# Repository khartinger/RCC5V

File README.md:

<table><tr><td></img></td><td>
Last modified: 2025-11-21 <br>   
<h1>Controlling model railroad components with DCC, MQTT and manually</h1>
<a href="LIESMICH.md">==> Deutsche Version</a>&nbsp; &nbsp; &nbsp; 
</td></tr></table>   

[Directly to the table of contents of this repository](#x20)   

# Introduction
Switching points is an important part of model railroading. There are many ways to control turnouts, uncouplers, disconnectable tracks and other components. Who doesn't want to be able to do this in different ways?    
The following image shows a part of an RCC control (RCC = Railway-Component-Control) with information display, switching and LED feedback.   
   
_Figure 1: Example user interface RCC control unit_   

## Traditional switching of turnouts etc.   
The simplest method of switching is, of course, to do it all by hand. In this case, you don't even need point machines. But with more distant or distributed components, this mode of operation quickly becomes cumbersome.   
For this reason, magnetic drives are usually used to switch the components. In the simplest case, the AC voltage is switched directly:   

_Figure 2: Direct switching of model railway components   
(turnout = turnout, uncoupler = uncoupler track, disconnectable track = disconnectable track)_   

However, direct switching of the AC voltage has disadvantages: There is no feedback on the actual switching status and automatic switching of several components is not possible.   
These disadvantages can be eliminated by commercial, digital control systems. Unfortunately, this is usually associated with considerable costs. For this reason, self-construction is an option, which also offers additional possibilities and flexibility.   

## How to do it better?
If you like building things yourself, you've come to the right place. The low-cost RCC (Railway Component Control) model railroad component controller presented here allows you to switch model railroad components in three different ways:   
* directly on the module or on the layout at the touch of a button   
* via DCC   
* via MQTT commands &uuml;over the WLAN   

In the standard version, up to 32 digital outputs and inputs are available. This means that a maximum of 16 two-way switches or 10 three-way switches etc. can be controlled. This number is normally sufficient for modules.   
Expansion of the system is generally possible and only depends on the I²C-IO expanders used.   

Some skills are advantageous for the successful use of the RCC system:   
* Soldering and some manual dexterity   
* Compiling and uploading a file to an ESP32 microcontroller   
* Basic knowledge of the open source [circuit board layout program KiCad](https://www.kicad.org/)   
* Basic knowledge of MQTT, if MQTT is to be used for control   

# How do I get started?
1. you should first get an overview of the [contents of this repository](#x20) and [the RCC system](#x30). This is provided in the chapters below in this manual.   
2. If the RCC system is the right choice, the requirements for your own system have to be defined:   
* Which components are needed?
* How many of each type are needed?
* Which DCC address for which device?   
_Example demo program_:   
1x uncoupler with DCC address 11, 1x two-way turnout (DCC 21), 1x three-way turnout (DCC 31 and 32), 1x traction current (DCC 41) and 1x flashing light (DCC 51).   
3. the next step is to manufacture the required components. How to do this is described in the chapter [“How do I start the RCC project?” (/fab/rcc0_start/README.md)](/fab/rcc0_start/README.md).   
4. the demo program is then adapted to your own system and the ESP32 microcontroller is programmed. This is described in chapter [`/software/rcc_demo1
/CUSTOMIZE_E.md`](/software/rcc_demo1/CUSTOMIZE_E.md).   
5. Finally, all components are wired and the entire system is tested.   

The detailed description of the [construction of module #12: “passing loop and siding”](/examples/module12/LIESMICH.md) can also be a great help.   

[To the top of the page](#up)   

# Overview
This repository deals with the production and use of components for controlling turnouts, uncouplers, disconnectable tracks etc. on an electric model railroad using DCC, MQTT or manually.   
The following topics are covered in various subdirectories:   

__Information about the system__   
* [How do I begin the RCC project?](/fab/rcc0_start/README.md)   
* [Electrical connection of railroad modules according to NEM 908D](/info/con_NEM908/README.md)   
* [Drill holes and covers for the front of the module](/info/frontpanel/README.md)   

__Manufacturing the system components__   
* [Manufacturing of Components for the power supply](/fab/rcc1_supply/README.md)   
* [Manufacturing of the ESP32-Shields](/fab/rcc2_esp32/README.md)   
* [Manufacturing of i2c boards](/fab/rcc3_i2c/README.md)   
* [Manufacturing of the switching blocks](/fab/rcc4_block/README.md)   
* [Manufacturing of additional boards](/fab/rcc5_add_ons/README.md)   
* [KiCad files of RCC components](/fab/kicad/README.md)   

__Software for the ESP32__   
* [MQTT commands for controlling the components](/software/mqtt/README.md)   
* [Overview of the demo software](/software/rcc_demo1/README.md)   
* [Customize the demo software to your own needs](/software/rcc_demo1/CUSTOMIZE_E.md)   
* [Structure of the demo software in detail](/software/rcc_demo1/DETAILS_E.md)   
* [Automatic execution of MQTT command sequences](/software/mqtt/README.md#x30)   

__Examples, use of the system__   
* [Example wiring of a turnout](/examples/exampleTurnout2/README.md)   
* [Construction of the “RCC block tester”](/examples/blocktester/README.md)   
* [Construction of module 12: “passing loop and siding”](/examples/module12/README.md)   
* [Construction of module 13: “reverse loop - west”](/examples/module13/README.md)   
* [Construction of module 14: “Two tracks to one track”](/examples/module14/README.md)   
* [Conversion of module M01: “Track 1 to 2 with goods shed (2010)”](/examples/module01/README.md)   

__Other practical ideas for modules and the like__   
* [module dust cover](/info/dust_cover/README.md)   

[To the top of the page](#up)   

# The RCC-system at a glance   
The RCC system has a modular structure and mechanically consists of a series of modules or blocks. Logically, it consists of six parts:   

1. __FEED-IN__ (power supply): Generation and provision of the supply voltage (here AC voltage) and the DCC signals for the RCC system by external components.   
2. __SUPPLY__ (module supply): The AC voltage, the traction current and the DCC signal for switching the magnetic articles are taken from the 25-pin plug according to NEM908 and a separate 5V DC voltage is generated.   
3. __&micro;C__ (microcontroller): The microcontroller, equipped with additional shields, is used to control the module. An ESP32 is used, which also handles communication with the MQTT broker.  
4. __I2C__: Connection between the microcontroller and the control blocks (RCC blocks). I2C I/O expander boards with PCF8574 are used for this purpose.   
5. __RCC block__: The control element for _a_ model railroad component with local operating and display elements.   
6. the __model railroad components__ such as turnouts, uncouplers and disconnectable tracks.   

_Figure 3: Block diagram for switching railroad components with 5V_   

By using the I2C-I/O-Expander-Boards it is possible to control several components:   
   
_Figure 4: Block diagram switching several railroad components with 5V_   

# Practical setup
Before e.g. the first switching of a turnout with RCC, some components must first be manufactured. How to do this is described in the chapter [“How do I start the RCC project?” (/fab/rcc0_start/README.md)](/fab/rcc0_start/README.md).   
The following figure shows an example of the modules required to control a three-way turnout:   
   
_Figure 5: Demo setup of an RCC-5V system: the individual parts_   

On the far left you can see the 25-pin connector with the 5V power supply (“SUPPLY”), behind it is the ESP32 with a 1.56 inch display (“&micro;C”). Two I2C-PCF8574 boards (“I2C”) are mounted in the front center, behind them the RCC block. On the right you can see a three-way turnout with two Fleischmann 640000 turnout drives. The electrical connection of the modules is made using 6-pin ribbon cables and wires.   

The following image shows an example of a possible front view of a module:   
   
_Figure 6: Example of module front view (= operating side)_   

[To the top of the page](#up)

# Example: Circuit diagram for switching a turnout with the RCC5V system
The following picture shows the electrical circuit diagram for controlling a turnout with DCC, MQTT or manually. The light green rectangles represent circuit boards developed in KiCad 8.0 and manufactured by [PCB Way](https://www.pcbway.com/). To do this, simply install the PCB Way plug-in in KiCad and the data required for production is then transferred with a click of the mouse.   

_Figure 7 Overall circuit diagram of the RCC-5V system_   

The upper third of the picture shows the supply of the DCC signal and the AC voltage (“FEED-IN”). The DCC signal for the traction current and the digital switching of the points is generated here with an old Roco-Multimaus, a 230V/18V/2.9A transformer [(e.g. BV00/026 from Conrad)](https://www.conrad.at/de/p/bv00-026-hochleistungstransformator-230-v-404288.html?refresh=true) is used for the AC voltage supply.   

The middle third of the picture shows the connection of the 25-pin connector to the microcontroller (5V and DCC signal) and to the RCC blocks (5V and AC signal). The ESP32 operates two separate I2C buses, one for the 1.56” OLED display (with 3.3V) and the second I2C bus for the PCF8574 boards (with 5V).   

Finally, the lower third of the picture shows the control of a two-way switch by an RCC block.   
The RCC block receives the switching command "Straight" (set WSA to 0V) or "Branch" (WSB=0V) from the microcontroller, switches the turnout and returns the state of the turnout (WRA=5V, WRB=0V for “Straight” or WRA=0V, WRB=5V for “Branch”). The RCC block also contains two buttons for local switching of the points and two LEDs for local display of the switching status of the points.   
You can also see that each RCC block requires a 5V and an AC voltage to switch the points.   

[To the top of the page](#up)

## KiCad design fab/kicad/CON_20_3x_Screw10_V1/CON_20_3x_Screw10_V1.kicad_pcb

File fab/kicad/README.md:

<table><tr><td></img></td><td>
Last modified: 2024-11-27 <br>   
<h1>KiCad files of RCC components</h1>
<a href="LIESMICH.md">==> Deutsche Version</a>&nbsp; &nbsp; &nbsp; 
</td></tr></table>    

# ... To Do ...

[To the top of the page](#up)

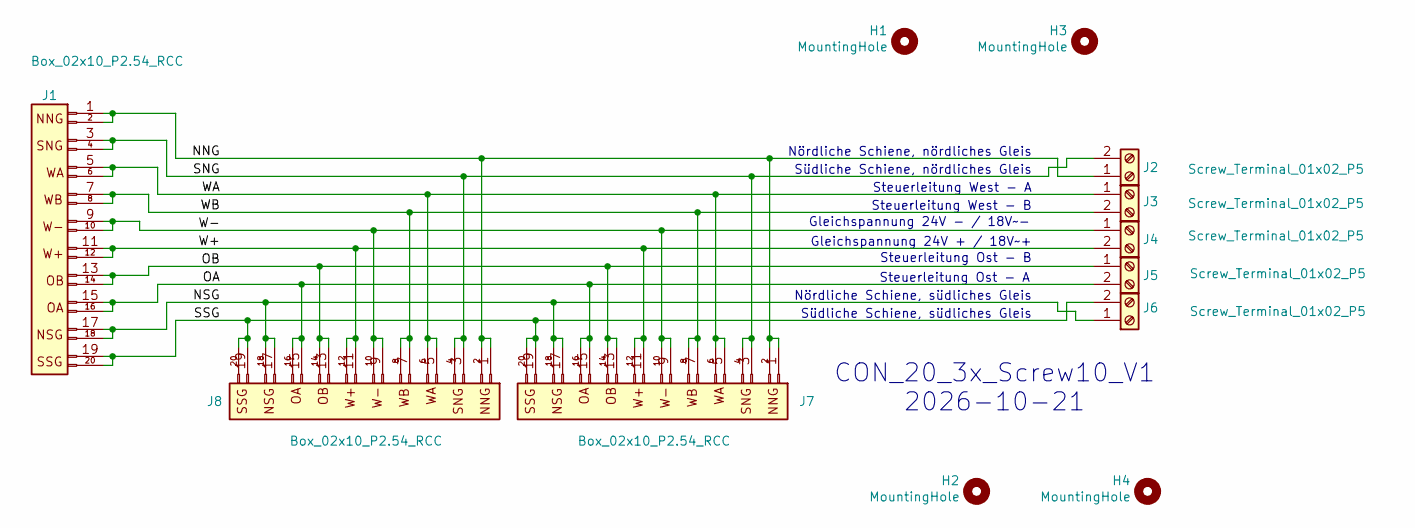
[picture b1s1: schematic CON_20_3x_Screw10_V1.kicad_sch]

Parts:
H1, H2, H3, H4: MountingHole; MountingHole_2.7mm_M2.5_DIN965_Pad_TopBottom
J1, J7, J8: Box_02x10_P2.54_RCC; Box_02x10_P2.54mm_Vertical_kh
J2, J3, J4, J5, J6: Screw_Terminal_01x02_P5

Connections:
/NNG: J1.1, J1.2, J2.1, J7.1, J7.2, J8.1, J8.2
/NSG: J1.17, J1.18, J6.1, J7.17, J7.18, J8.17, J8.18
/OA: J1.15, J1.16, J5.2, J7.15, J7.16, J8.15, J8.16
/OB: J1.13, J1.14, J5.1, J7.13, J7.14, J8.13, J8.14
/SNG: J1.3, J1.4, J2.2, J7.3, J7.4, J8.3, J8.4
/SSG: J1.19, J1.20, J6.2, J7.19, J7.20, J8.19, J8.20
/W+: J1.11, J1.12, J4.2, J7.11, J7.12, J8.11, J8.12
/W-: J1.9, J1.10, J4.1, J7.9, J7.10, J8.9, J8.10
/WA: J1.5, J1.6, J3.1, J7.5, J7.6, J8.5, J8.6
/WB: J1.7, J1.8, J3.2, J7.7, J7.8, J8.7, J8.8

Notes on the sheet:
CON_20_3x_Screw10_V1 2026-10-21
Südliche Schiene, südliches Gleis
Südliche Schiene, nördliches Gleis
Gleichspannung 24V - / 18V~-
Nördliche Schiene, nördliches Gleis
Steuerleitung West - A
Steuerleitung Ost - B
Steuerleitung West - B
Gleichspannung 24V + / 18V~+
Nördliche Schiene, südliches Gleis
Steuerleitung Ost - A

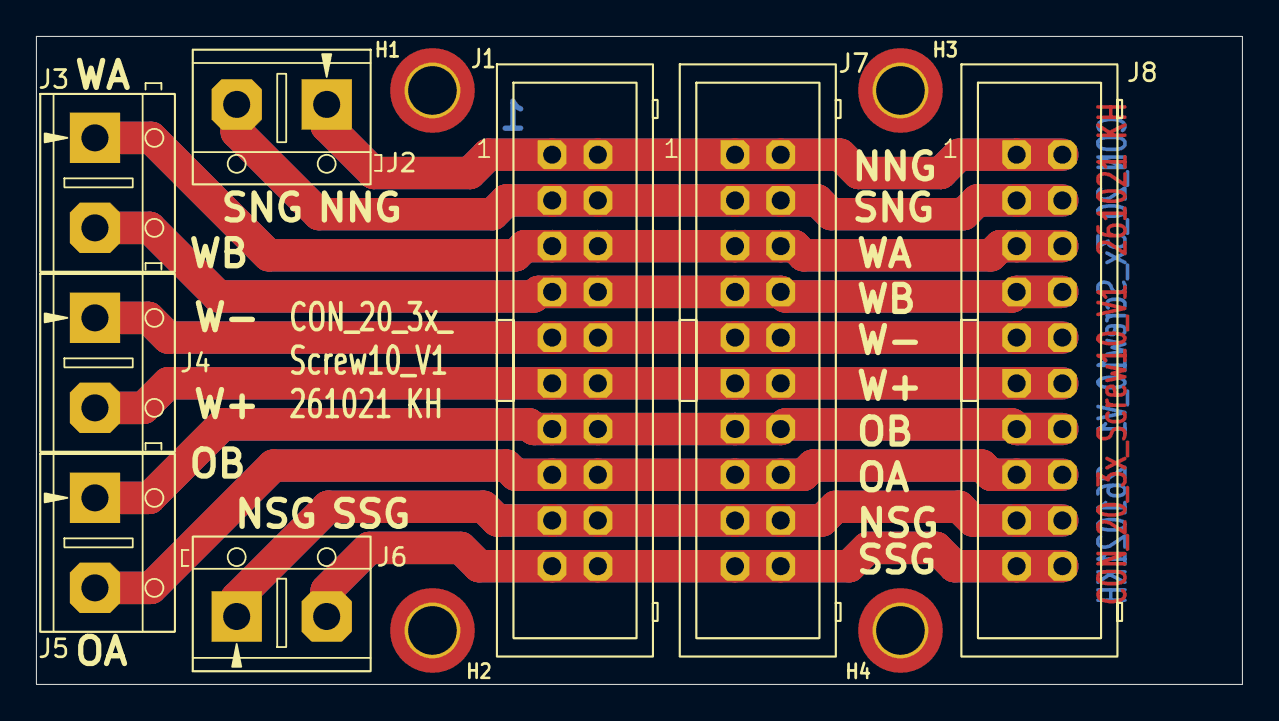
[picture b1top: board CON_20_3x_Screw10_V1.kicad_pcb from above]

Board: 2 copper layers, 67.0 x 36.0 mm, 12 parts (0 on the bottom side), 10 nets.

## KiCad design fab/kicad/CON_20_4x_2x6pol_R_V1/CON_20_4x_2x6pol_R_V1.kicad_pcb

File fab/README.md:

<table><tr><td></img></td><td>

Last modified: 2025-07-20 <br>   
<h1>Assembly instructions for modules, circuit boards and 3D parts</h1>
<a href="LIESMICH.md">==> Deutsche Version</a>&nbsp; &nbsp; &nbsp; 
</td></tr></table>   

<a href="LIESMICH.md"><b> Sorry! This page is currently only available in German.</b></a>   

[To the top of the page](#up)

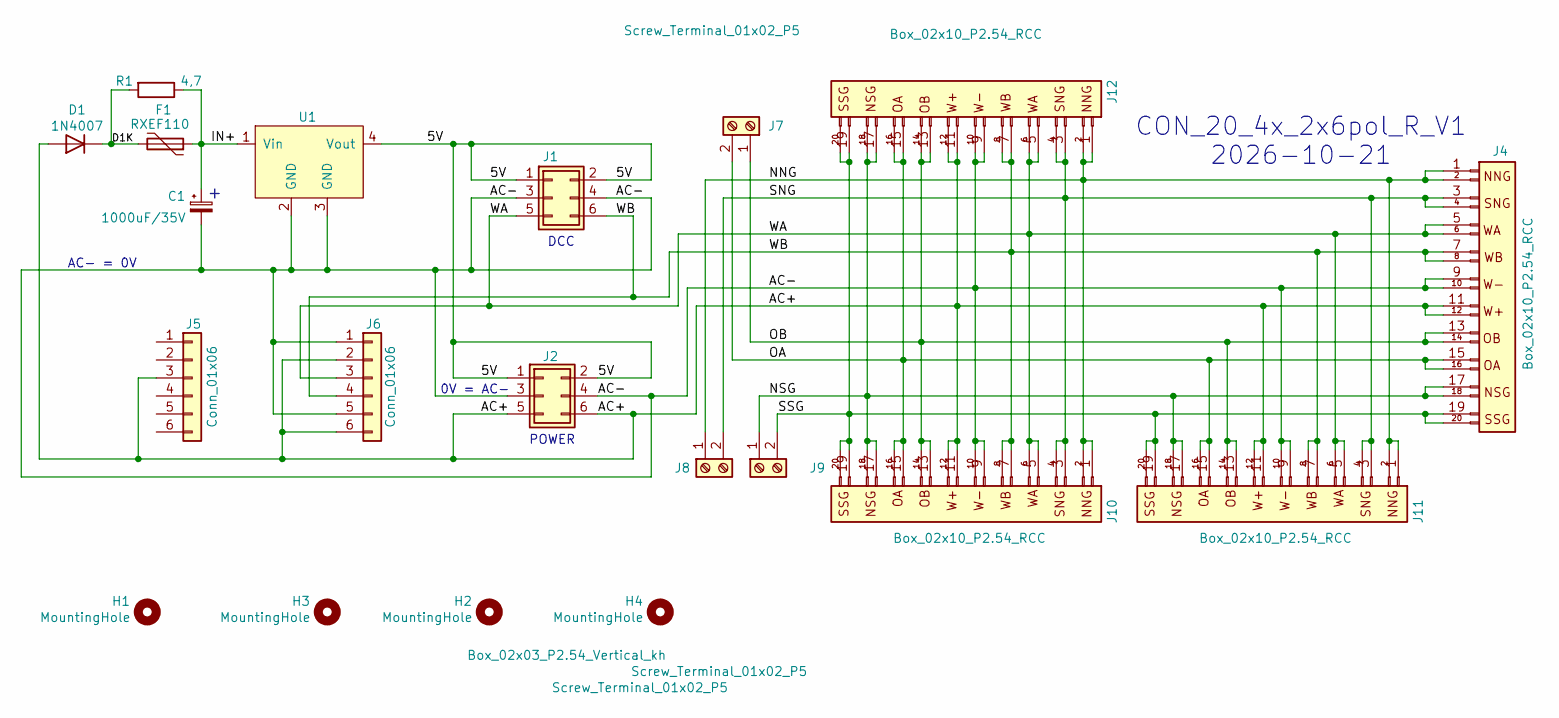
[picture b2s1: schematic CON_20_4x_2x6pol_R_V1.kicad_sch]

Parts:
C1: 1000uF/35V; CP_Radial_L16.8mm_D10.0mm_P5.08mm_Horizontal_small_2
D1: 1N4007; D_DO-41_SOD81_P12.7mm_Horizontal_kh
F1: RXEF110; Fuse_PTC_P5.08mm_D12.8mm_Horizontal_kh
H1, H2, H3, H4: MountingHole; MountingHole_2.7mm_M2.5_DIN965_Pad_TopBottom
J1: Box_02x03_P2.54_Vertical; Box_02x03_P2.54mm_Vertical_kh
J2: Box_02x03_P2.54_Vertical_kh; Box_02x03_P2.54mm_Vertical_kh
J4, J10, J11, J12: Box_02x10_P2.54_RCC; Box_02x10_P2.54mm_Vertical_kh
J5, J6: Conn_01x06; PinSocket_1x06_P2.54mm_Vertical_kh
J7, J8: Screw_Terminal_01x02_P5
J9: Screw_Terminal_01x02_P5; Screw_Terminal_01x02_P5_8
R1: 4,7; R_Axial_Power_L25.0mm_W6.4mm_P27.94mm_kh
U1: DCDC_StepDown_LM2596; DCDC_StepDown_LM2596_PinsOnly

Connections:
/5V: J1.1, J1.2, J2.1, J2.2, U1.4 (Vout)
/AC+: D1.2 (A), J2.5, J2.6, J4.11, J4.12, J5.3 (Pin_3_3), J6.2, J6.6, J10.11, J10.12, J11.11, J11.12, J12.11, J12.12
/AC-: C1.2, J1.3, J1.4, J2.3, J2.4, J4.9, J4.10, J6.1, J6.5, J10.9, J10.10, J11.9, J11.10, J12.9, J12.10, U1.2 (GND), U1.3 (GND)
/D1K: D1.1 (K), F1.2, R1.2
/IN+: C1.1, F1.1, R1.1, U1.1 (Vin)
/NNG: J4.1, J4.2, J8.1, J10.1, J10.2, J11.1, J11.2, J12.1, J12.2
/NSG: J4.17, J4.18, J9.1, J10.17, J10.18, J11.17, J11.18, J12.17, J12.18
/OA: J4.15, J4.16, J7.2, J10.15, J10.16, J11.15, J11.16, J12.15, J12.16
/OB: J4.13, J4.14, J7.1, J10.13, J10.14, J11.13, J11.14, J12.13, J12.14
/SNG: J4.3, J4.4, J8.2, J10.3, J10.4, J11.3, J11.4, J12.3, J12.4
/SSG: J4.19, J4.20, J9.2, J10.19, J10.20, J11.19, J11.20, J12.19, J12.20
/WA: J1.5, J4.5, J4.6, J6.3, J10.5, J10.6, J11.5, J11.6, J12.5, J12.6
/WB: J1.6, J4.7, J4.8, J6.4, J10.7, J10.8, J11.7, J11.8, J12.7, J12.8

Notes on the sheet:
AC- = 0V
POWER
CON_20_4x_2x6pol_R_V1 2026-10-21
0V = AC-
DCC

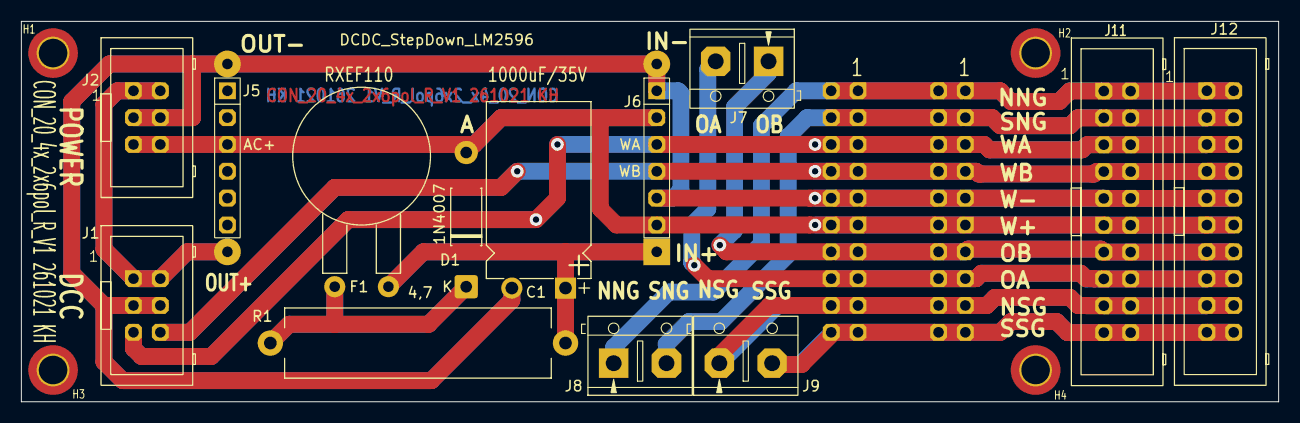
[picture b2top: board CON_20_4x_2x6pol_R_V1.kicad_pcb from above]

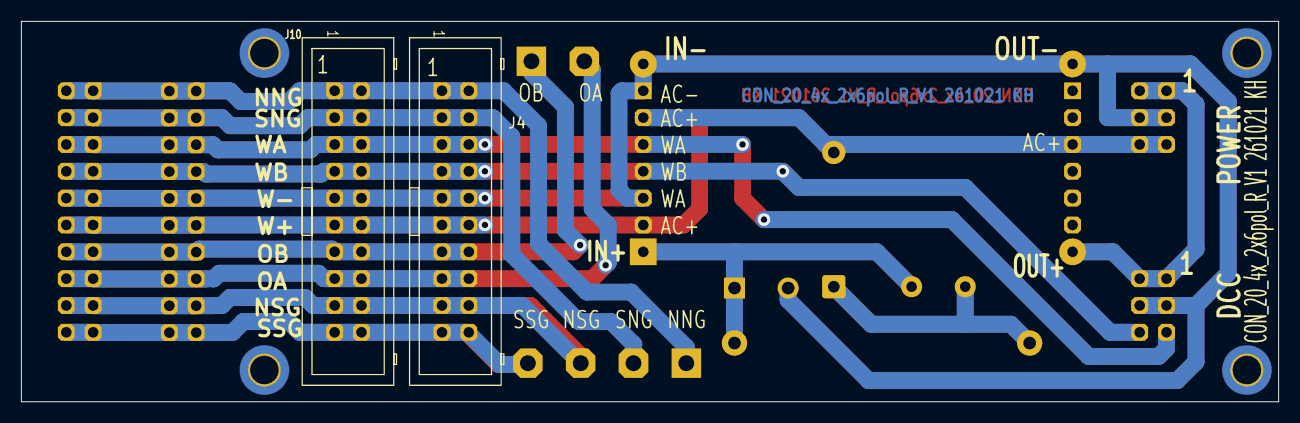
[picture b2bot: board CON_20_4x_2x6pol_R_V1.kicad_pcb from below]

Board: 2 copper layers, 119.0 x 36.0 mm, 20 parts (2 on the bottom side), 13 nets.

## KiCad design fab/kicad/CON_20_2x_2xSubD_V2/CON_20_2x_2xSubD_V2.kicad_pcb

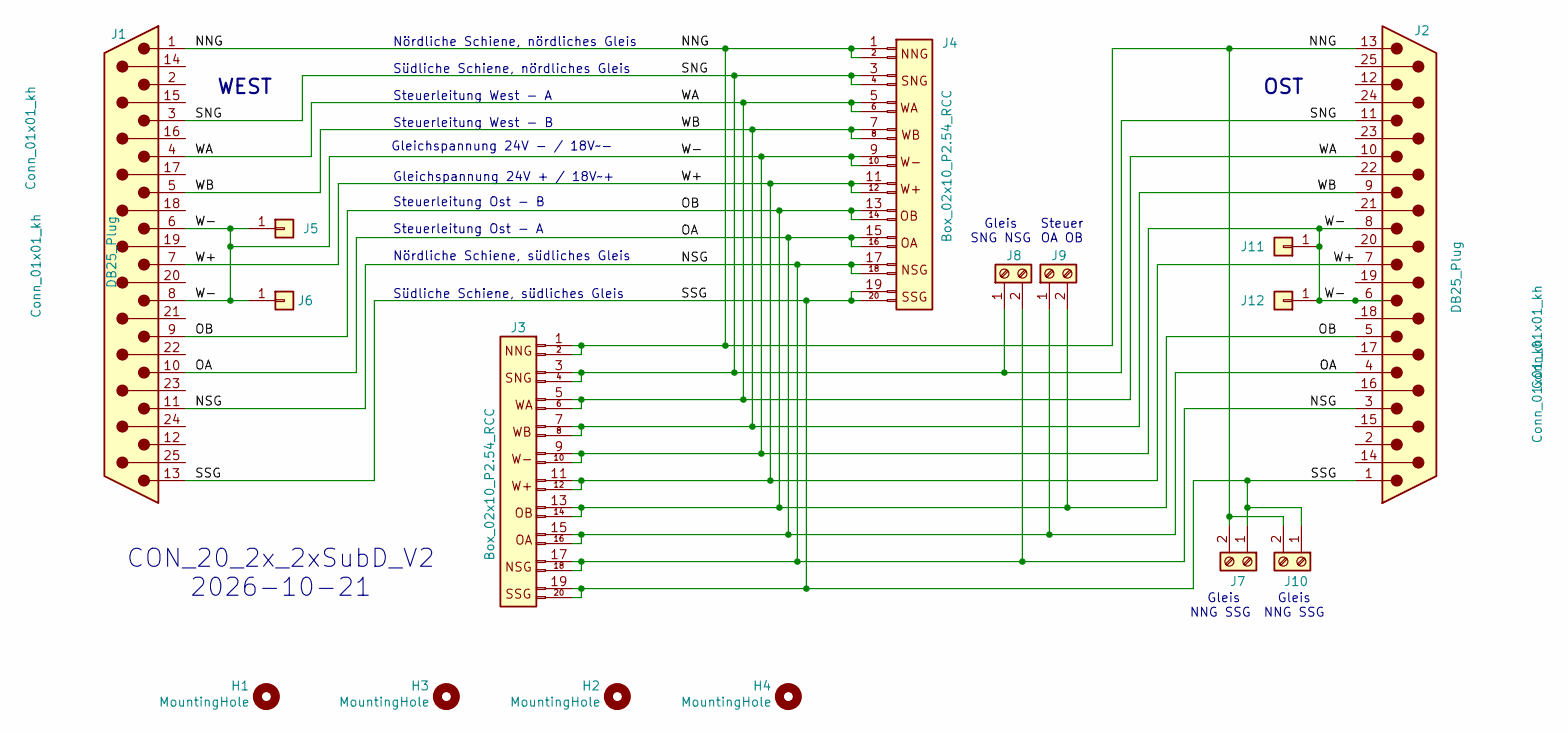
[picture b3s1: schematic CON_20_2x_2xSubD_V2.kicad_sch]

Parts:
H1, H2, H3, H4: MountingHole; MountingHole_2.7mm_M2.5_DIN965_Pad_TopBottom
J1, J2: DB25_Plug; DSUB-25_Male_Horizontal_P2.77x2.84mm_EdgePinOffset7.70mm_Ho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
J3, J4: Box_02x10_P2.54_RCC; Box_02x10_P2.54mm_Vertical_kh
J5, J6: Conn_01x01_kh; Pin_D0.8mm_W1.2mm
J7, J8, J9, J10: Screw_Terminal_01x02_P5
J11, J12: Conn_01x01_kh; Pin_D0.9mm_W1.4mm

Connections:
/NNG: J1.1, J2.13, J3.1, J3.2, J4.1, J4.2, J7.2, J10.2
/NSG: J1.11, J2.3, J3.17, J3.18, J4.17, J4.18, J8.2
/OA: J1.10, J2.4, J3.15, J3.16, J4.15, J4.16, J9.1
/OB: J1.9, J2.5, J3.13, J3.14, J4.13, J4.14, J9.2
/SNG: J1.3, J2.11, J3.3, J3.4, J4.3, J4.4, J8.1
/SSG: J1.13, J2.1, J3.19, J3.20, J4.19, J4.20, J7.1, J10.1
/W+: J1.7, J2.7, J3.11, J3.12, J4.11, J4.12
/W-: J1.6, J1.8, J2.6, J2.8, J3.9, J3.10, J4.9, J4.10, J5.1 (Pin_1_1), J6.1 (Pin_1_1), J11.1 (Pin_1_1), J12.1 (Pin_1_1)
/WA: J1.4, J2.10, J3.5, J3.6, J4.5, J4.6
/WB: J1.5, J2.9, J3.7, J3.8, J4.7, J4.8

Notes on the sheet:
CON_20_2x_2xSubD_V2 2026-10-21
Südliche Schiene, südliches Gleis
Südliche Schiene, nördliches Gleis
Gleichspannung 24V - / 18V~-
Nördliche Schiene, nördliches Gleis
OST
Steuerleitung West - A
Steuerleitung Ost - B
Steuerleitung West - B
Gleis SNG NSG
WEST
Gleichspannung 24V + / 18V~+
Nördliche Schiene, südliches Gleis
Steuer OA OB
Gleis NNG SSG
Gleis NNG SSG
Steuerleitung Ost - A

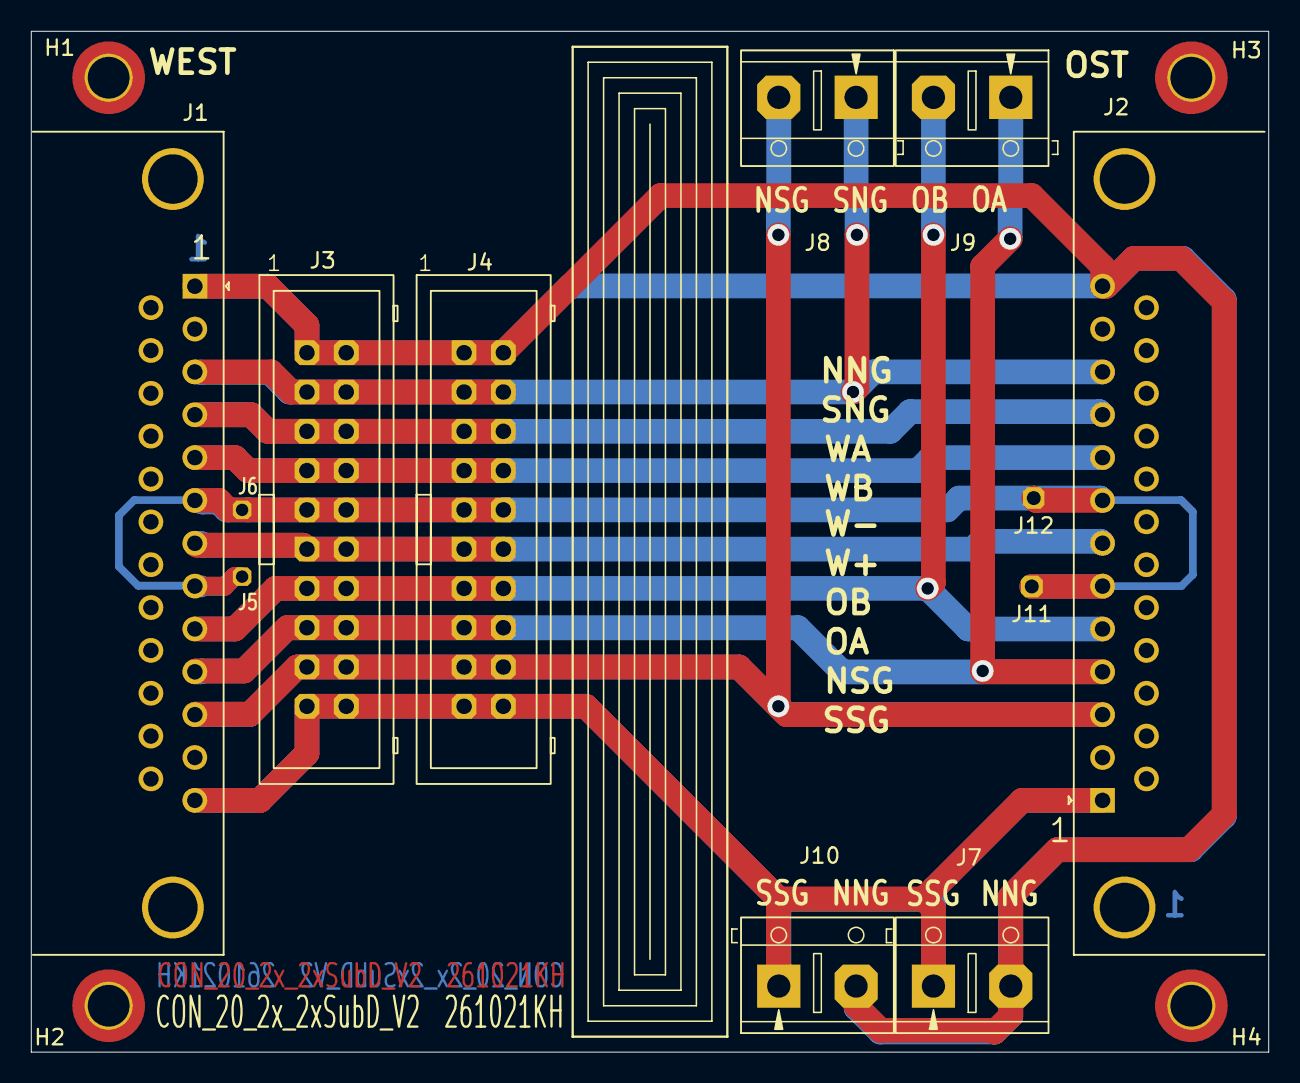
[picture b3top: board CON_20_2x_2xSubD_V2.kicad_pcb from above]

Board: 2 copper layers, 80.0 x 66.0 mm, 16 parts (0 on the bottom side), 10 nets.

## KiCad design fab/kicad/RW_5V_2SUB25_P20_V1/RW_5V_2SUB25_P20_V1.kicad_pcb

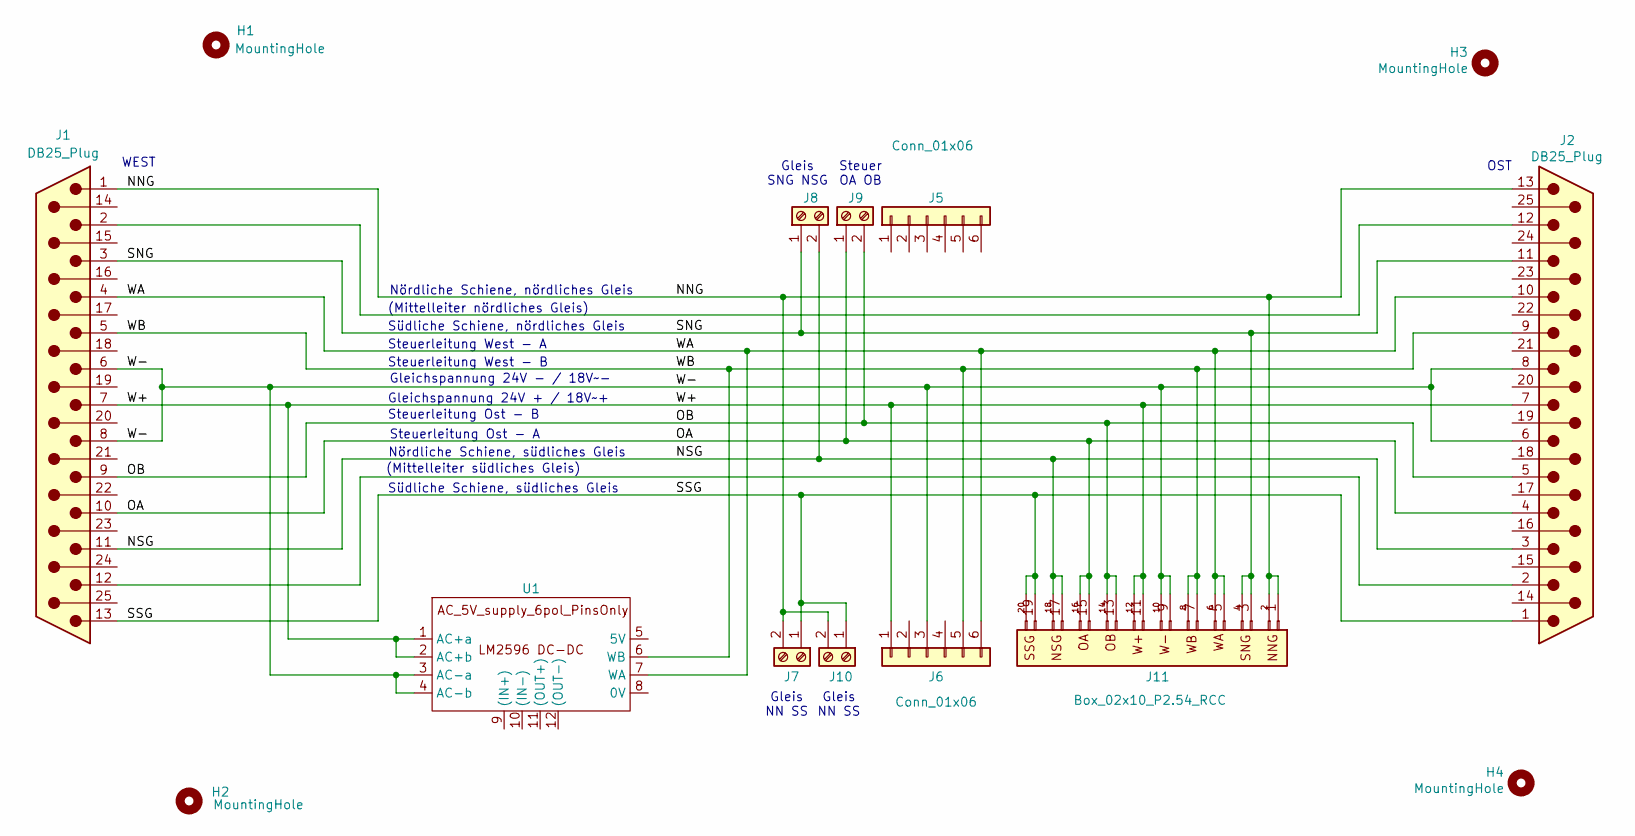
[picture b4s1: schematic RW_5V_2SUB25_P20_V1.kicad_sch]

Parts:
H1, H2, H3, H4: MountingHole; MountingHole_2.7mm_M2.5_DIN965_Pad_TopBottom
J1, J2: DB25_Plug; DSUB-25_Male_Horizontal_P2.77x2.84mm_EdgePinOffset7.70mm_Ho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
J5, J6: Conn_01x06; PinSocket_1x06_P2.54mm_Vertical_1.1_kh
J7, J8, J9, J10: Screw_Terminal_01x02_P5
J11: Box_02x10_P2.54_RCC; Box_02x10_P2.54mm_Vertical_kh
U1: AC_5V_supply_6pol_PinsOnly

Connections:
/NNG: J1.1, J2.13, J7.2, J10.2, J11.1, J11.2
/NSG: J1.11, J2.3, J8.2, J11.17, J11.18
/OA: J1.10, J2.4, J9.1, J11.15, J11.16
/OB: J1.9, J2.5, J9.2, J11.13, J11.14
/SNG: J1.3, J2.11, J8.1, J11.3, J11.4
/SSG: J1.13, J2.1, J7.1, J10.1, J11.19, J11.20
/W+: J1.7, J2.7, J6.1, J11.11, J11.12, U1.1 (AC+a), U1.2 (AC+b)
/W-: J1.6, J1.8, J2.6, J2.8, J6.3, J11.9, J11.10, U1.3 (AC-a), U1.4 (AC-b)
/WA: J1.4, J2.10, J6.6, J11.5, J11.6, U1.7 (WA)
/WB: J1.5, J2.9, J6.5, J11.7, J11.8, U1.6 (WB)
unnamed: J1.2, J2.12
unnamed: J1.12, J2.2

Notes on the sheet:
Gleis SNG NSG
Südliche Schiene, südliches Gleis
Südliche Schiene, nördliches Gleis
Steuer OA OB
Gleichspannung 24V - / 18V~-
Nördliche Schiene, nördliches Gleis
(Mittelleiter südliches Gleis)
Steuerleitung West - A
Gleis NN SS
Steuerleitung Ost - B
Steuerleitung West - B
WEST
(Mittelleiter nördliches Gleis)
Nördliche Schiene, südliches Gleis
Gleichspannung 24V + / 18V~+
OST
Steuerleitung Ost - A

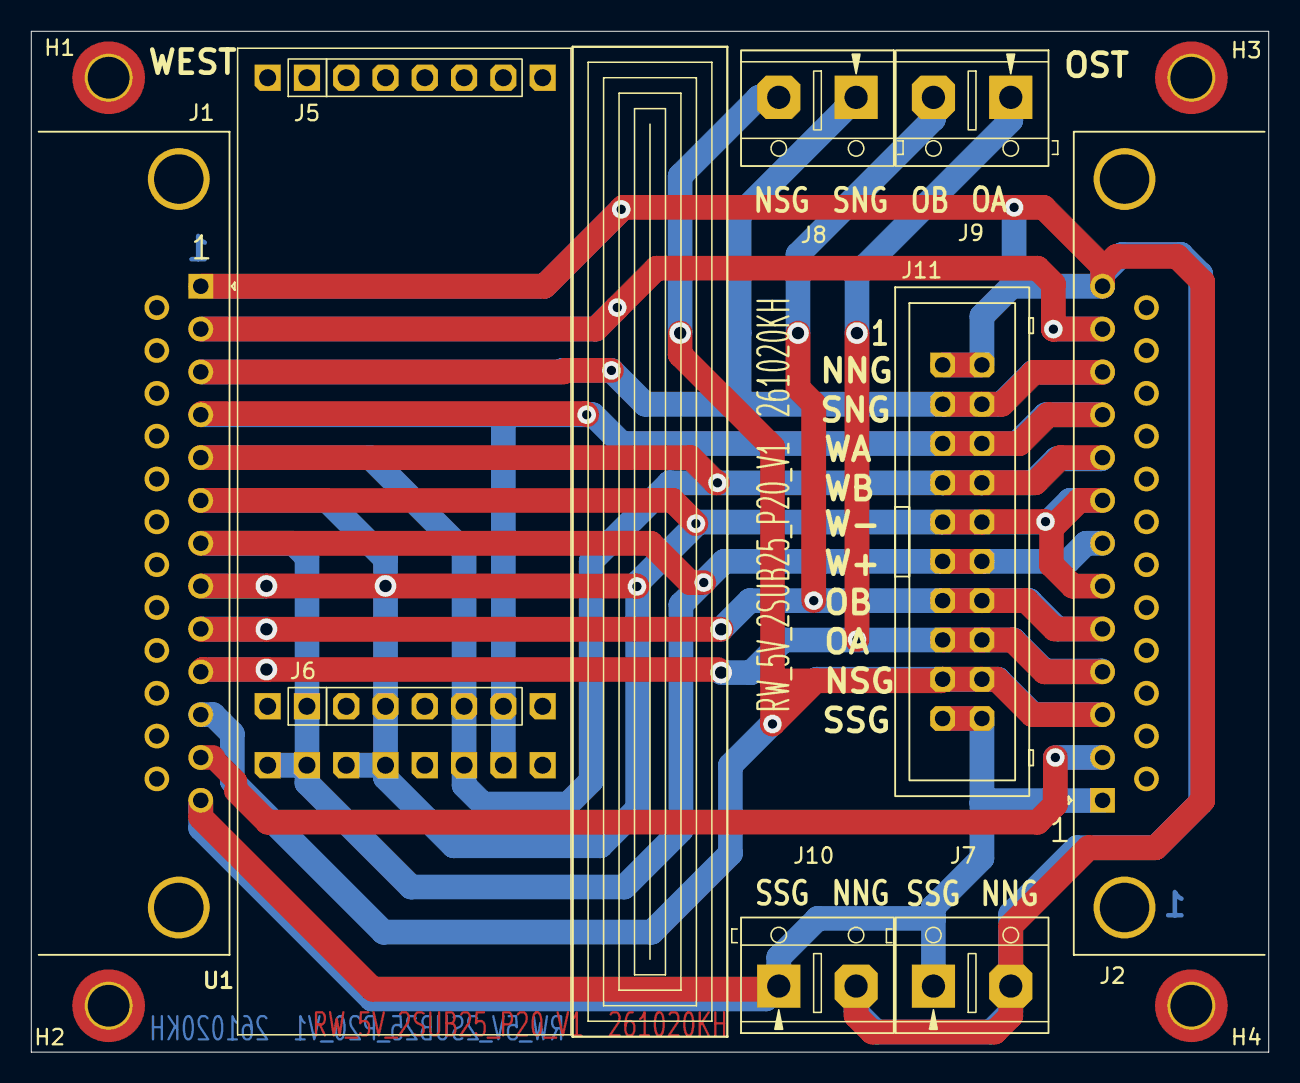
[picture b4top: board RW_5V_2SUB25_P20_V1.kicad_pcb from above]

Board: 2 copper layers, 80.0 x 66.0 mm, 14 parts (0 on the bottom side), 12 nets.

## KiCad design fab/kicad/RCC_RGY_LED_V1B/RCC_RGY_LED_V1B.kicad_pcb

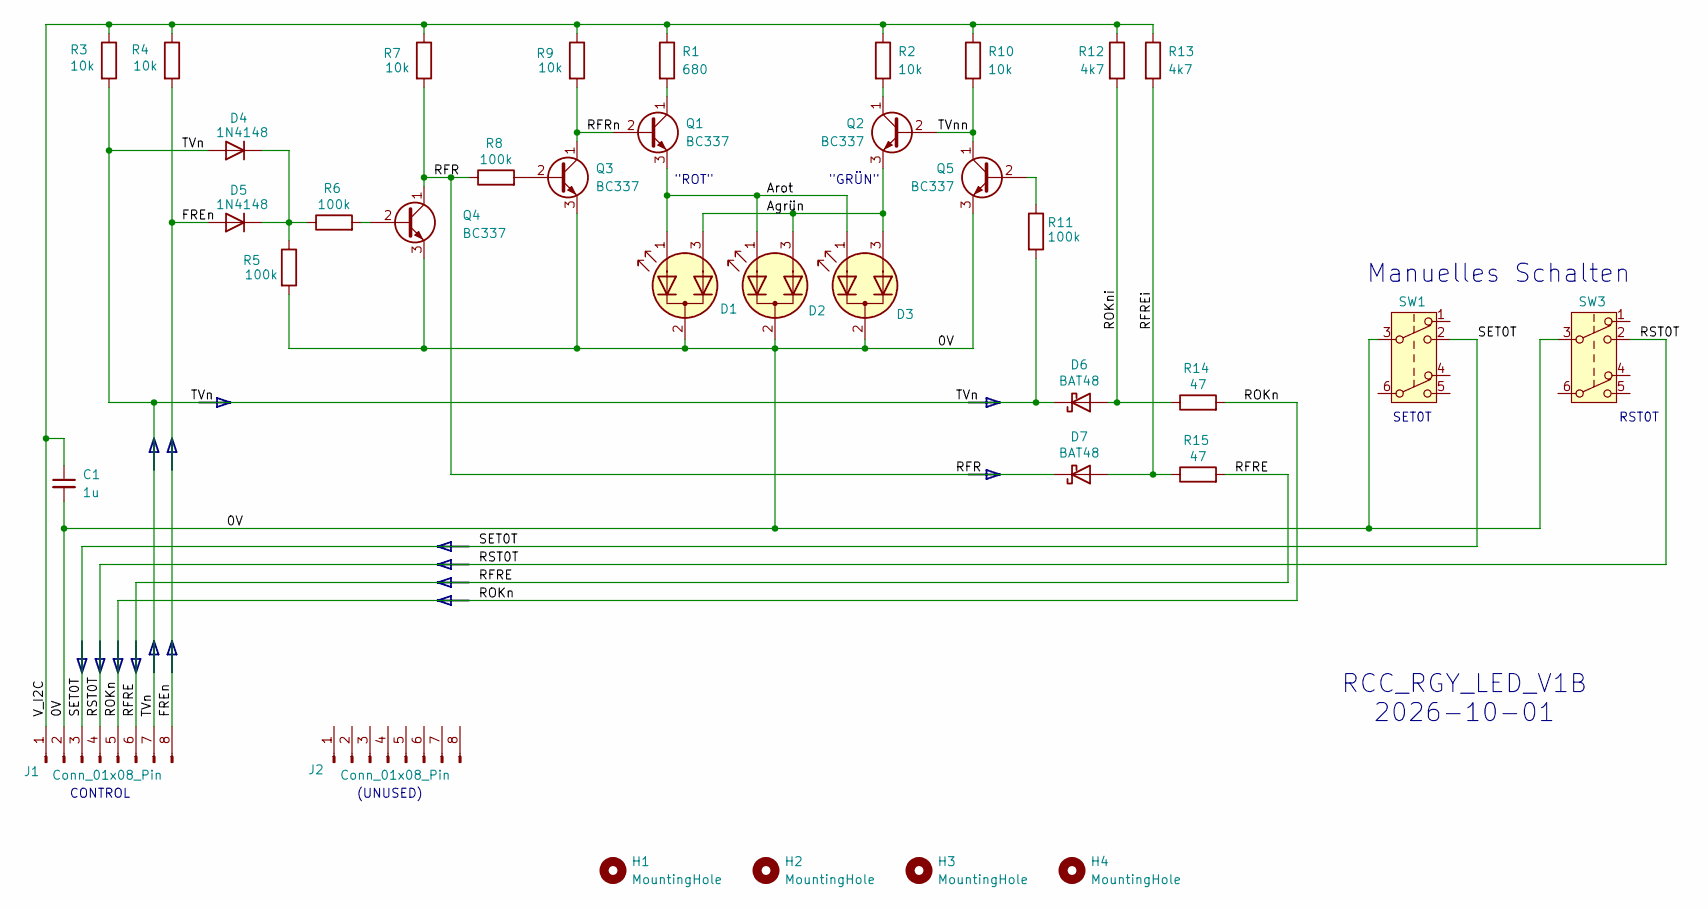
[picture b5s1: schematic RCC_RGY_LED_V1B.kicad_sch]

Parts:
C1: 1u; C_L4.3mm_D2.8mm_P5.08mm_kh
D1, D2, D3: LED_Dual_AKA; LED_D5.0mm-3
D4: 1N4148; D_DO-35_P3.81mm_Vertical_AnodeUp_kh
D5: 1N4148; D_DO-35_P2.0mm_Vertical_AnodeUp_kh
D6, D7: BAT48; D_DO-35_SOD27_P2.54mm_Vertical_AnodeUp_kh
H1, H2, H3, H4: MountingHole; MountingHole_2.2mm_M2_Pad_TopBottom_kh
J1, J2: Conn_01x08_Pin; PinSocket_1x08_P2.54mm_Vertical_11mm_kh
Q1, Q2, Q3, Q4, Q5: BC337; TO-92_Inline_Wide_custom
R1: 680; R_Axial_DIN0204_L3.6mm_D1.6mm_P2.54mm_Vertical_kh
R2, R3, R9, R10: 10k; R_Axial_DIN0204_L3.6mm_D1.6mm_P2.54mm_Vertical
R4: 10k; R_Axial_DIN0204_L3.6mm_D1.6mm_P17.78mm_Horizontal
R5, R11: 100k; R_Axial_DIN0204_L3.6mm_D1.6mm_P2.54mm_Vertical
R6: 100k; R_Axial_DIN0204_L3.6mm_D1.6mm_P2.54mm_Vertical_kh
R7: 10k; R_Axial_DIN0204_L3.6mm_D1.6mm_P7.62mm_Horizontal
R8: 100k; R_Axial_DIN0204_L3.6mm_D1.6mm_P3.81mm_Vertical_kh
R12: 4k7; R_Axial_DIN0204_L3.6mm_D1.6mm_P2.54mm_Vertical
R13: 4k7; R_Axial_DIN0204_L3.6mm_D1.6mm_P3.81mm_Vertical_kh
R14: 47; R_Axial_DIN0204_L3.6mm_D1.6mm_P2.54mm_Vertical_kh
R15: 47; R_Axial_DIN0204_L3.6mm_D1.6mm_P7.62mm_Horizontal
SW1, SW3: SW_Push_DPDT_8x8

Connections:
/0V: C1.2, D1.2 (K), D2.2 (K), D3.2 (K), J1.2, Q3.3 (E), Q4.3 (E), Q5.3 (E), R5.2, SW1.3 (C), SW3.3 (C)
/Agrün: D1.3 (A2), D2.3 (A2), D3.3 (A2), Q2.3 (E)
/Arot: D1.1 (A1), D2.1 (A1), D3.1 (A1), Q1.3 (E)
/FREn: D5.2 (A), J1.8, R4.2
/RFR: D7.1 (K), Q4.1 (C), R7.2, R8.1
/RFRE: J1.6, R15.2
/RFREi: D7.2 (A), R13.2, R15.1
/RFRn: Q1.2 (B), Q3.1 (C), R9.2
/ROKn: J1.5, R14.2
/ROKni: D6.2 (A), R12.2, R14.1
/RST0T: J1.4, SW3.2 (B)
/SET0T: J1.3, SW1.2 (B)
/TVn: D4.2 (A), D6.1 (K), J1.7, R3.2, R11.2
/TVnn: Q2.2 (B), Q5.1 (C), R10.2
/V_I2C: C1.1, J1.1, R1.1, R2.1, R3.1, R4.1, R7.1, R9.1, R10.1, R12.1, R13.1
unnamed: D4.1 (K), D5.1 (K), R5.1, R6.1
unnamed: Q1.1 (C), R1.2
unnamed: Q2.1 (C), R2.2
unnamed: Q3.2 (B), R8.2
unnamed: Q4.2 (B), R6.2
unnamed: Q5.2 (B), R11.1

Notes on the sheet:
(UNUSED)
SET0T
Manuelles Schalten
"GRÜN"
RCC_RGY_LED_V1B 2026-10-01
CONTROL
"ROT"
RST0T

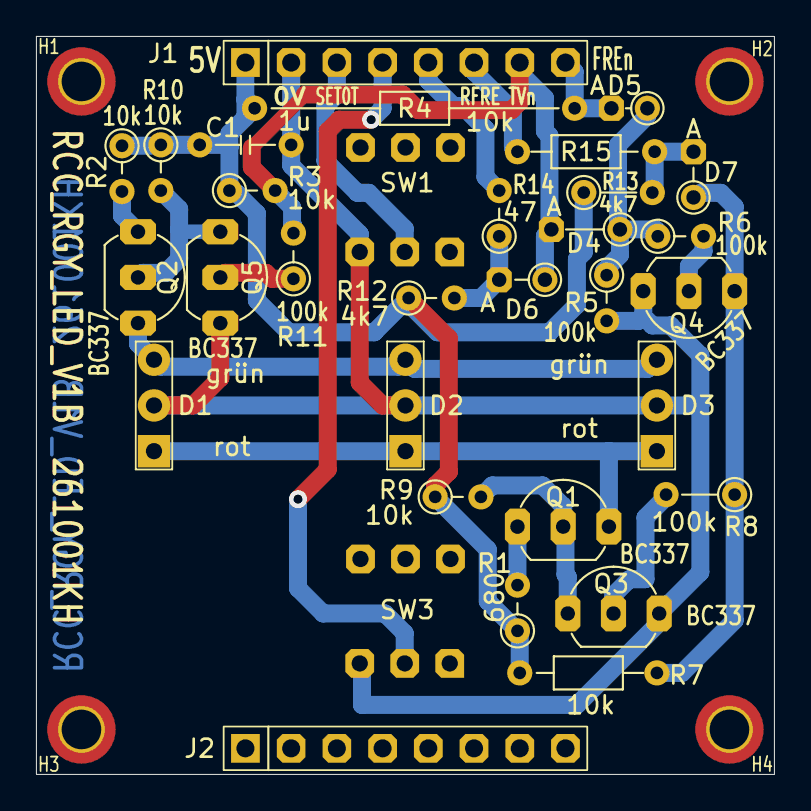
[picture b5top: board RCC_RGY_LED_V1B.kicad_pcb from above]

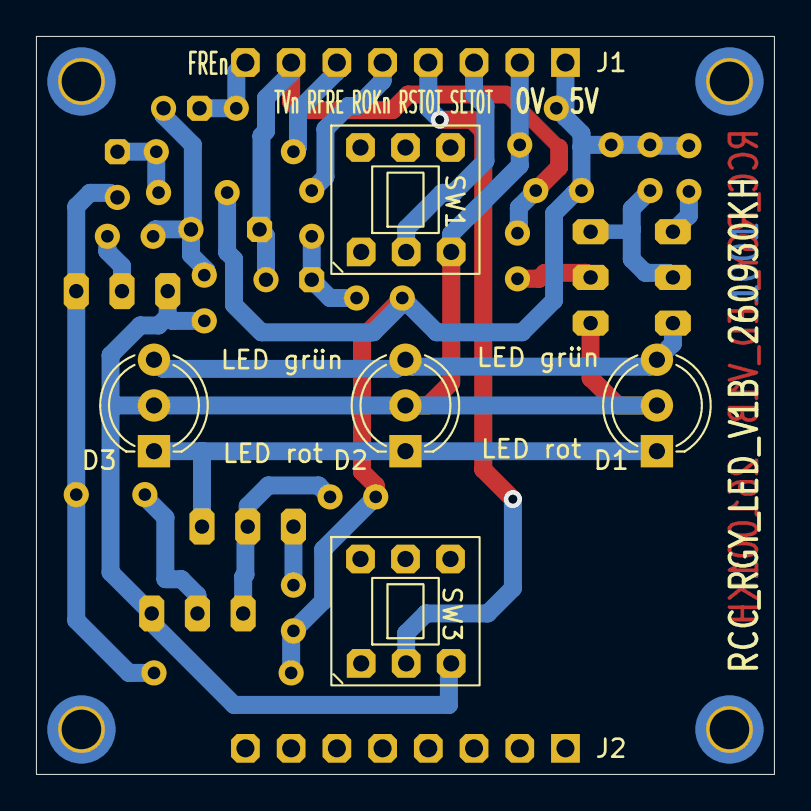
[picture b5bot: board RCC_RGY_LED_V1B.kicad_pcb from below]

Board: 2 copper layers, 41.0 x 41.0 mm, 36 parts (5 on the bottom side), 21 nets.

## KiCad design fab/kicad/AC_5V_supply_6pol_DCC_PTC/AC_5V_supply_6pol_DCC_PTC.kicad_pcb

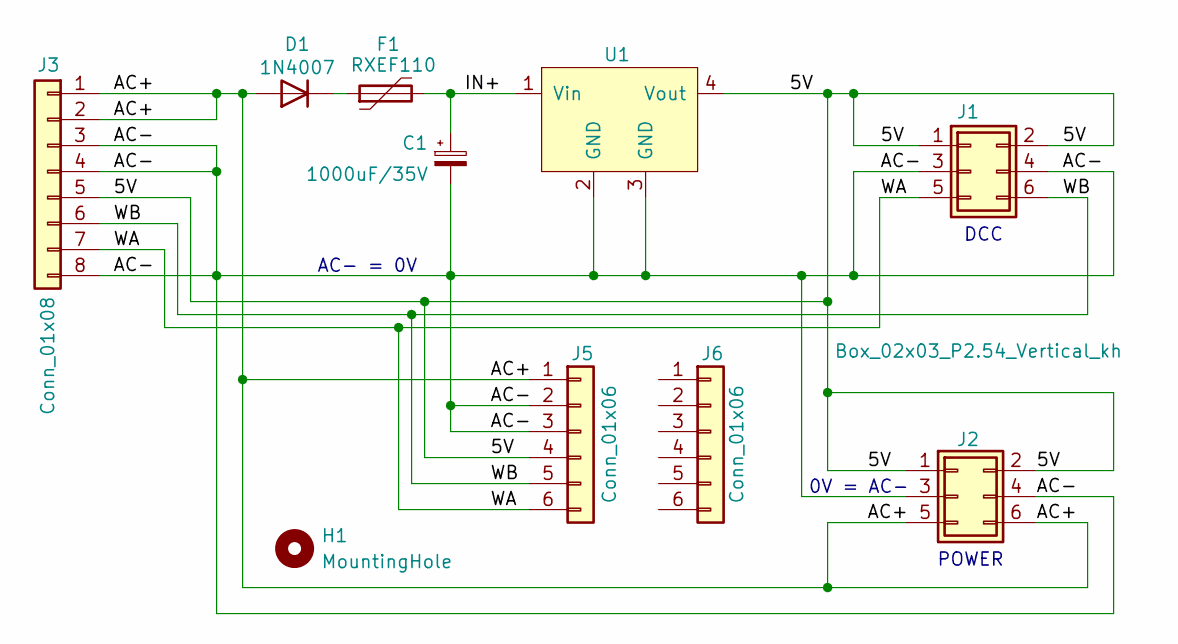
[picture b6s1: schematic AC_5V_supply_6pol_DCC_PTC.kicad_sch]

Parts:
C1: 1000uF/35V; CP_Radial_L16.8mm_D10.0mm_P5.08mm_Horizontal_small_2
D1: 1N4007; D_DO-41_P5.08mm_Vertical_AnodeUp_kh
F1: RXEF110; Fuse_PTC_P5.08mm_D12.8mm_Horizontal_kh
H1: MountingHole; MountingHole_2.7mm_M2.5_DIN965_Pad_TopBottom
J1: Box_02x03_P2.54_Vertical; Box_02x03_P2.54mm_Vertical_kh
J2: Box_02x03_P2.54_Vertical_kh; Box_02x03_P2.54mm_Vertical_kh
J3: Conn_01x08; PinSocket_1x08_P2.54mm_Vertical_kh
J5, J6: Conn_01x06; PinSocket_1x06_P2.54mm_Vertical_kh
U1: DCDC_StepDown_LM2596; DCDC_StepDown_LM2596_PinsOnly

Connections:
/5V: J1.1, J1.2, J2.1, J2.2, J3.5, J5.4, U1.4 (Vout)
/AC+: D1.2 (A), J2.5, J2.6, J3.1, J3.2, J5.1
/AC-: C1.2, J1.3, J1.4, J2.3, J2.4, J3.3, J3.4, J3.8, J5.2, J5.3, U1.2 (GND), U1.3 (GND)
/IN+: C1.1, F1.2, U1.1 (Vin)
/WA: J1.5, J3.7, J5.6
/WB: J1.6, J3.6, J5.5
unnamed: D1.1 (K), F1.1

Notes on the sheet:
AC- = 0V
POWER
0V = AC-
DCC

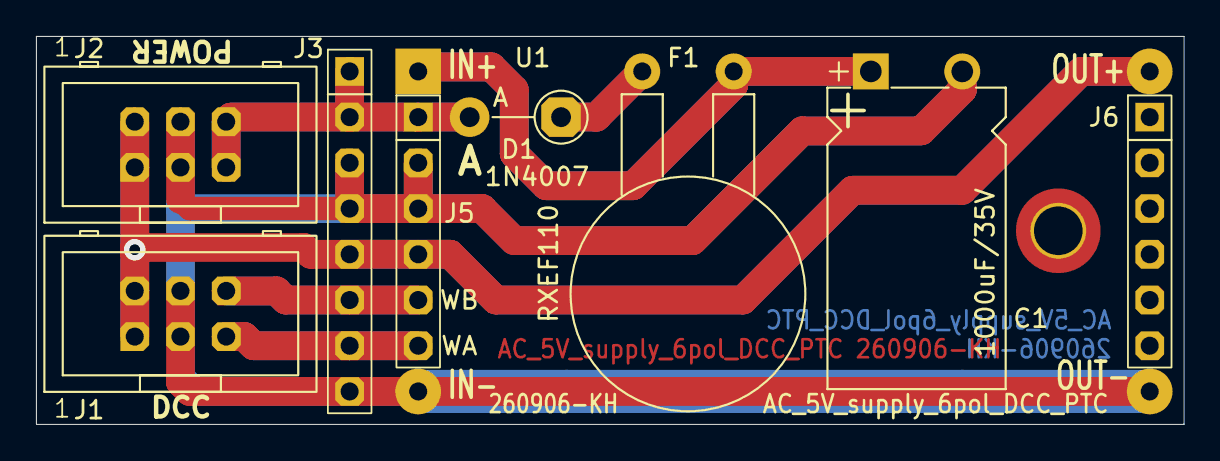
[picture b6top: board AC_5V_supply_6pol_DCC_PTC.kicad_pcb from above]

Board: 2 copper layers, 63.8 x 21.6 mm, 10 parts (0 on the bottom side), 7 nets.
